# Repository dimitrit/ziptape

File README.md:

# ZipTape: Fast Tape Interface for the PAL-1

ZipTape is a fast cassete interface for the PAL-1 system, originally described in the February 1977 issue of BYTE magazine[^1], and later adapted for the KIM-1[^2].

This implementation is intended to plug in to the PAL-1 RIOT Expansion Module[^3].

[^1]: Daniel Lomax, _‘The Impossible Dream Cassette Interface’_, BYTE, 2.2 (1977), 82–85.  
[^2]: Lew Edwards, _‘FAST CASSETTE INTERFACE DESCRIPTION’_, 1978 <http://retro.hansotten.nl/6502-sbc/kim-1-manuals-and-software/kim-1-articles/kim-1-ziptape/> [accessed 25 January 2023].
[^3]: Liu Ganning, _‘RIOT EXPANSION’_, 2021 <http://pal.aibs.ws/assets/RIOT_expansion_manual.pdf> [accessed 25 January 2023].

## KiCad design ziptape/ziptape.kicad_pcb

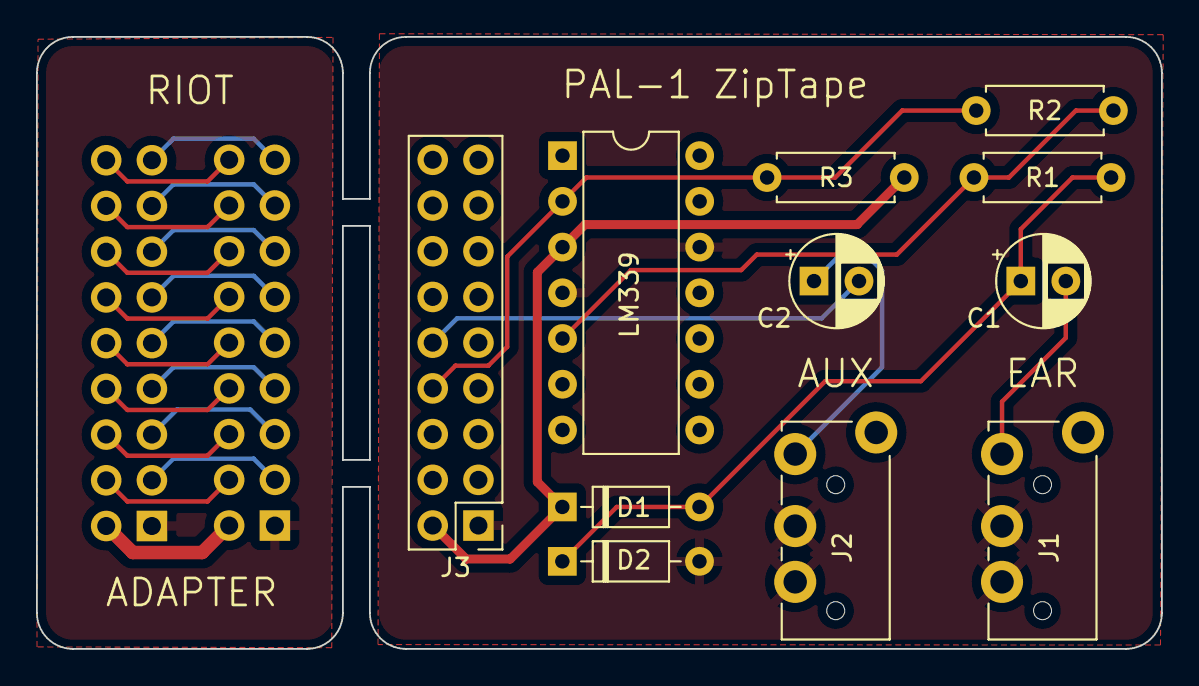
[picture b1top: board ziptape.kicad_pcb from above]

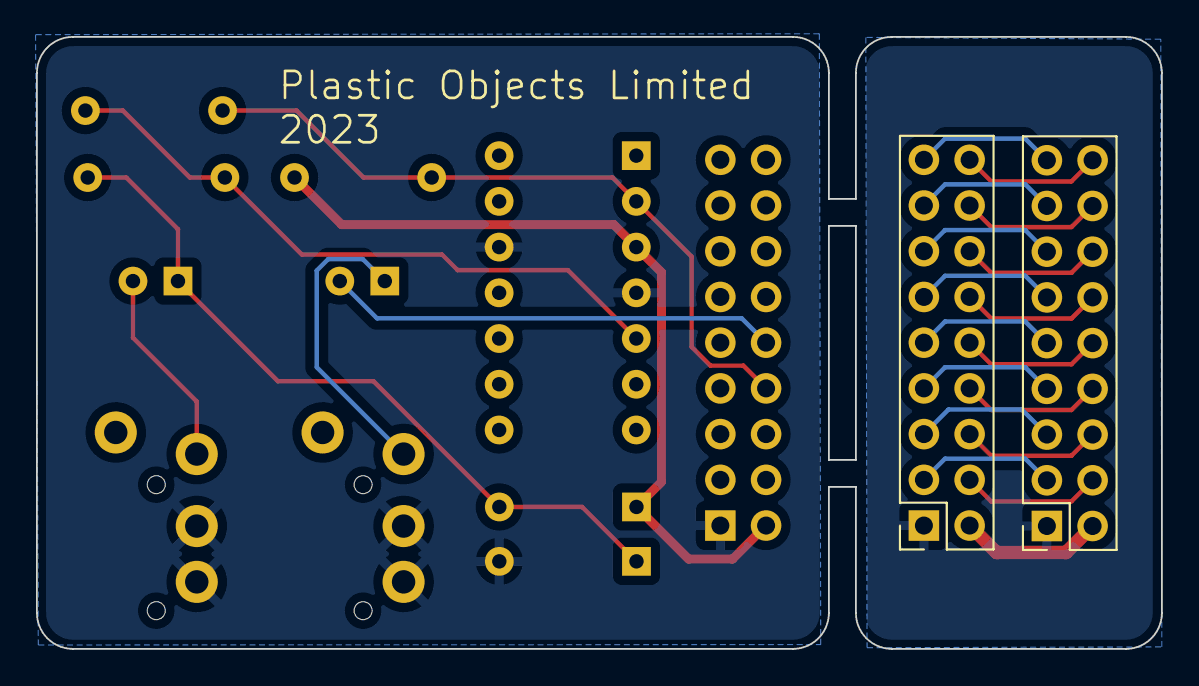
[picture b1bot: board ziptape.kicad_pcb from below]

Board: 2 copper layers, 62.5 x 34.0 mm, 13 parts (2 on the bottom side), 26 nets.

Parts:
C1: 0.18uF; CP_Radial_D5.0mm_P2.50mm
C2: 0.5uF; CP_Radial_D5.0mm_P2.50mm
D1, D2: 1N4148; D_DO-35_SOD27_P7.62mm_Horizontal
J1: Cassette_Playback; Jack_3.5mm_4Pole_TRRS
J2: Cassette_Record; Jack_3.5mm_4Pole_TRRS
J3: Conn_RIOT; PinHeader_2x09_P2.54mm_Vertical
J4: Conn_Adapter_A; PinSocket_2x09_P2.54mm_Vertical
J5: Conn_Adapter_B; PinSocket_2x09_P2.54mm_Vertical
R1: 15K; R_Axial_DIN0207_L6.3mm_D2.5mm_P7.62mm_Horizontal
R2: 15M; R_Axial_DIN0207_L6.3mm_D2.5mm_P7.62mm_Horizontal
R3: 3K; R_Axial_DIN0207_L6.3mm_D2.5mm_P7.62mm_Horizontal
U1: LM339; DIP-14_W7.62mm

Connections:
/A_GND: J4.1, J5.1
/A_PA0: J4.3, J5.3
/A_PA1: J4.5, J5.5
/A_PA2: J4.7, J5.7
/A_PA3: J4.9, J5.9
/A_PA4: J4.11, J5.11
/A_PA5: J4.13, J5.13
/A_PA6: J4.15, J5.15
/A_PA7: J4.17, J5.17
/A_PB0: J4.4, J5.4
/A_PB1: J4.6, J5.6
/A_PB2: J4.8, J5.8
/A_PB3: J4.10, J5.10
/A_PB4: J4.12, J5.12
/A_PB5: J4.14, J5.14
/A_PB6: J4.16, J5.16
/A_PB7: J4.18, J5.18
/A_VCC: J4.2, J5.2
GND: D2.2 (A), J1.G, J1.R, J2.G, J2.R, J3.1, U1.4 (-), U1.12 (V-)
unnamed: C1.1, D1.2 (A), D2.1 (K), R1.1
unnamed: C1.2, J1.T
unnamed: C2.1, J2.T
unnamed: R1.2, R2.1, U1.5 (+)
PB2: J3.8, R2.2, R3.1, U1.2
PB3: C2.2, J3.10
VCC: D1.1 (K), J3.2, R3.2, U1.3 (V+)

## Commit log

2023-01-25 Add schematic
2023-01-25 Add printable version of schematic
2023-01-26 Assign footprints
2023-01-26 Add readme
2023-01-26 Add git attributes
2023-01-27 Add layout
2023-01-27 Update schema
2023-01-28 Add 3d model to audio socket
2023-01-28 Update audio sockets
2023-01-28 Add images
2023-01-28 Add gerbers
